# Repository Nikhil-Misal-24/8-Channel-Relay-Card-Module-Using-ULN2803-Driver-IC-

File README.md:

ULN2803 Based 8-Channel Relay Driver Module
8-Channel Relay Card Using ULN2803 Darlington Driver

This project presents the design and implementation of an 8-Channel Relay Driver Module using the ULN2803 Darlington Transistor Array. 
The module is designed to allow low-power microcontroller signals to safely control high-voltage or high-current loads such as lamps, motors, 
fans, and other electrical devices.
The ULN2803 IC acts as a relay driver, enabling reliable switching by amplifying the current from digital control signals. This design 
simplifies interfacing with microcontrollers like Arduino, ESP32, Raspberry Pi, AVR, and PIC, making it ideal for embedded systems and automation applications.
The PCB is designed to provide a compact, efficient, and easy-to-integrate relay control solution for projects involving home automation, industrial control, 
IoT systems, and smart devices.

Key Features
8-Channel relay control system
Driver circuit based on ULN2803 Darlington array
Compatible with microcontrollers (Arduino, ESP32, Raspberry Pi)
Built-in flyback diode protection for relay coils
Compact and reliable PCB layout
Suitable for high-voltage load switching

Applications
Home Automation Systems
Industrial Control Panels
IoT-based Switching Systems
Smart Agriculture Projects
Motor and Pump Control
Lighting Control Systems

Repository Includes
Schematic Design
PCB Layout Files
Gerber Files for PCB Manufacturing
Bill of Materials (BOM)

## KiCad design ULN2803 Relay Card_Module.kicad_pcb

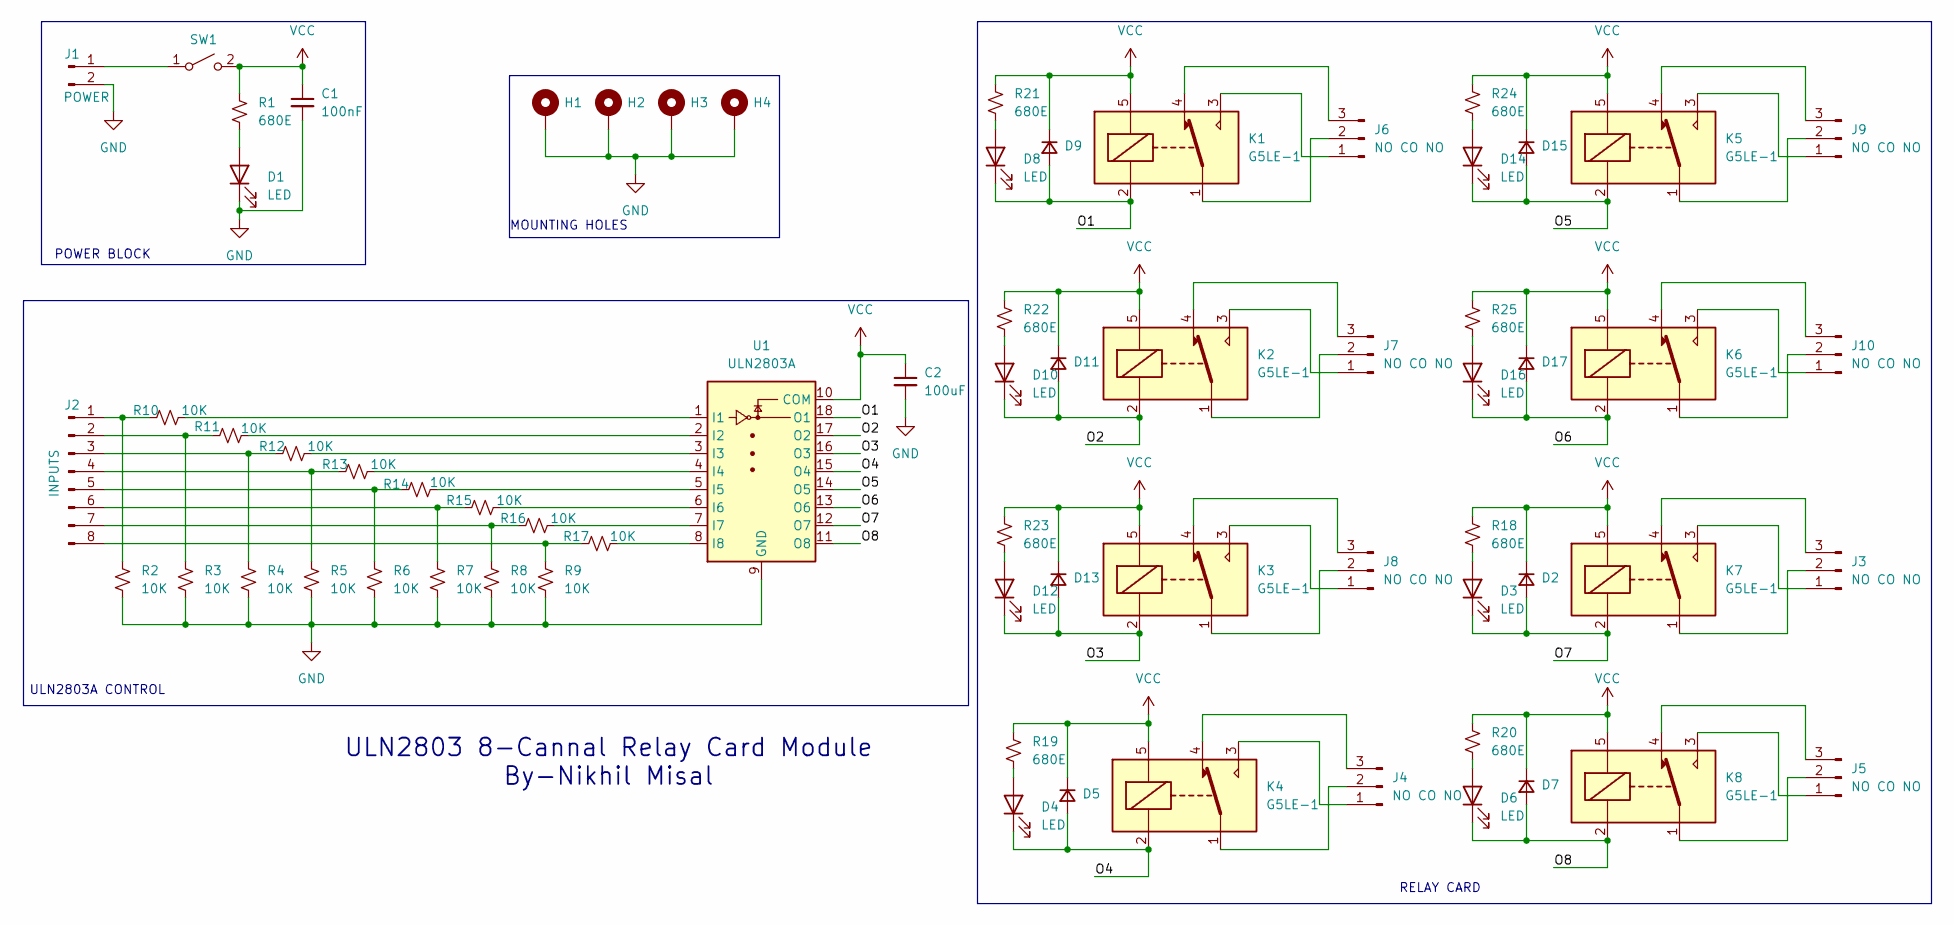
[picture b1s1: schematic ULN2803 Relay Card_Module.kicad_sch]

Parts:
C1: 100nF; C_0805_2012Metric
C2: 100uF; C_0805_2012Metric
D1, D3, D4, D6, D8, D10, D12, D14, D16: LED; LED_1206_3216Metric
D2, D5, D7, D9, D11, D13, D15, D17: D_Small; D_1206_3216Metric
H1, H2, H3, H4: MountingHole_Pad; MountingHole_2.5mm_Pad_Via
J1: POWER; JST_NV_B02P-NV_1x02_P5.00mm_Vertical
J2: INPUTS; PinHeader_1x08_P2.54mm_Vertical
J3, J4, J5, J6, J7, J8, J9, J10: NO CO NO; JST_NV_B03P-NV_1x03_P5.00mm_Vertical
K1, K2, K3, K4, K5, K6, K7, K8: G5LE-1; Relay_SPDT_Omron-G5LE-1
R1, R18, R19, R20, R21, R22, R23, R24, R25: 680E; R_0805_2012Metric
R2, R3, R4, R5, R6, R7, R8, R9, R10, R11, R12, R13, R14, R15, R16, R17: 10K; R_0805_2012Metric
SW1: SW_SPST; SW_DIP_SPSTx01_Slide_6.7x4.1mm_W6.73mm_P2.54mm_LowProfile_J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
U1: ULN2803A; DIP-18_W7.62mm_LongPads

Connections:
/O1: D8.1 (K), D9.2 (A), K1.2, U1.18 (O1)
/O2: D10.1 (K), D11.2 (A), K2.2, U1.17 (O2)
/O3: D12.1 (K), D13.2 (A), K3.2, U1.16 (O3)
/O4: D4.1 (K), D5.2 (A), K4.2, U1.15 (O4)
/O5: D14.1 (K), D15.2 (A), K5.2, U1.14 (O5)
/O6: D16.1 (K), D17.2 (A), K6.2, U1.13 (O6)
/O7: D2.2 (A), D3.1 (K), K7.2, U1.12 (O7)
/O8: D6.1 (K), D7.2 (A), K8.2, U1.11 (O8)
GND: C1.2, C2.2, D1.1 (K), H1.1, H2.1, H3.1, H4.1, J1.2, R2.2, R3.2, R4.2, R5.2, R6.2, R7.2, R8.2, R9.2, U1.9 (GND)
unnamed: D1.2 (A), R1.2
unnamed: D3.2 (A), R18.2
unnamed: D4.2 (A), R19.2
unnamed: D6.2 (A), R20.2
unnamed: D8.2 (A), R21.2
unnamed: D10.2 (A), R22.2
unnamed: D12.2 (A), R23.2
unnamed: D14.2 (A), R24.2
unnamed: D16.2 (A), R25.2
unnamed: J1.1, SW1.1 (A)
unnamed: J2.1, R2.1, R10.1
unnamed: J2.2, R3.1, R11.1
unnamed: J2.3, R4.1, R12.1
unnamed: J2.4, R5.1, R13.1
unnamed: J2.5, R6.1, R14.1
unnamed: J2.6, R7.1, R15.1
unnamed: J2.7, R8.1, R16.1
unnamed: J2.8, R9.1, R17.1
unnamed: J3.1, K7.3
unnamed: J3.2, K7.1
unnamed: J3.3, K7.4
unnamed: J4.1, K4.3
unnamed: J4.2, K4.1
unnamed: J4.3, K4.4
unnamed: J5.1, K8.3
unnamed: J5.2, K8.1
unnamed: J5.3, K8.4
unnamed: J6.1, K1.3
unnamed: J6.2, K1.1
unnamed: J6.3, K1.4
unnamed: J7.1, K2.3
unnamed: J7.2, K2.1
unnamed: J7.3, K2.4
unnamed: J8.1, K3.3
unnamed: J8.2, K3.1
unnamed: J8.3, K3.4
unnamed: J9.1, K5.3
unnamed: J9.2, K5.1
unnamed: J9.3, K5.4
unnamed: J10.1, K6.3
unnamed: J10.2, K6.1
unnamed: J10.3, K6.4
unnamed: R10.2, U1.1 (I1)
unnamed: R11.2, U1.2 (I2)
unnamed: R12.2, U1.3 (I3)
unnamed: R13.2, U1.4 (I4)
unnamed: R14.2, U1.5 (I5)
unnamed: R15.2, U1.6 (I6)
unnamed: R16.2, U1.7 (I7)
unnamed: R17.2, U1.8 (I8)
VCC: C1.1, C2.1, D2.1 (K), D5.1 (K), D7.1 (K), D9.1 (K), D11.1 (K), D13.1 (K), D15.1 (K), D17.1 (K), K1.5, K2.5, K3.5, K4.5, K5.5, K6.5, K7.5, K8.5, R1.1, R18.1, R19.1, R20.1, R21.1, R22.1, R23.1, R24.1, R25.1, SW1.2 (B), U1.10 (COM)

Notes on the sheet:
RELAY CARD
ULN2803A CONTROL
POWER BLOCK
MOUNTING HOLES
ULN2803 8-Cannal Relay Card Module By-Nikhil Misal

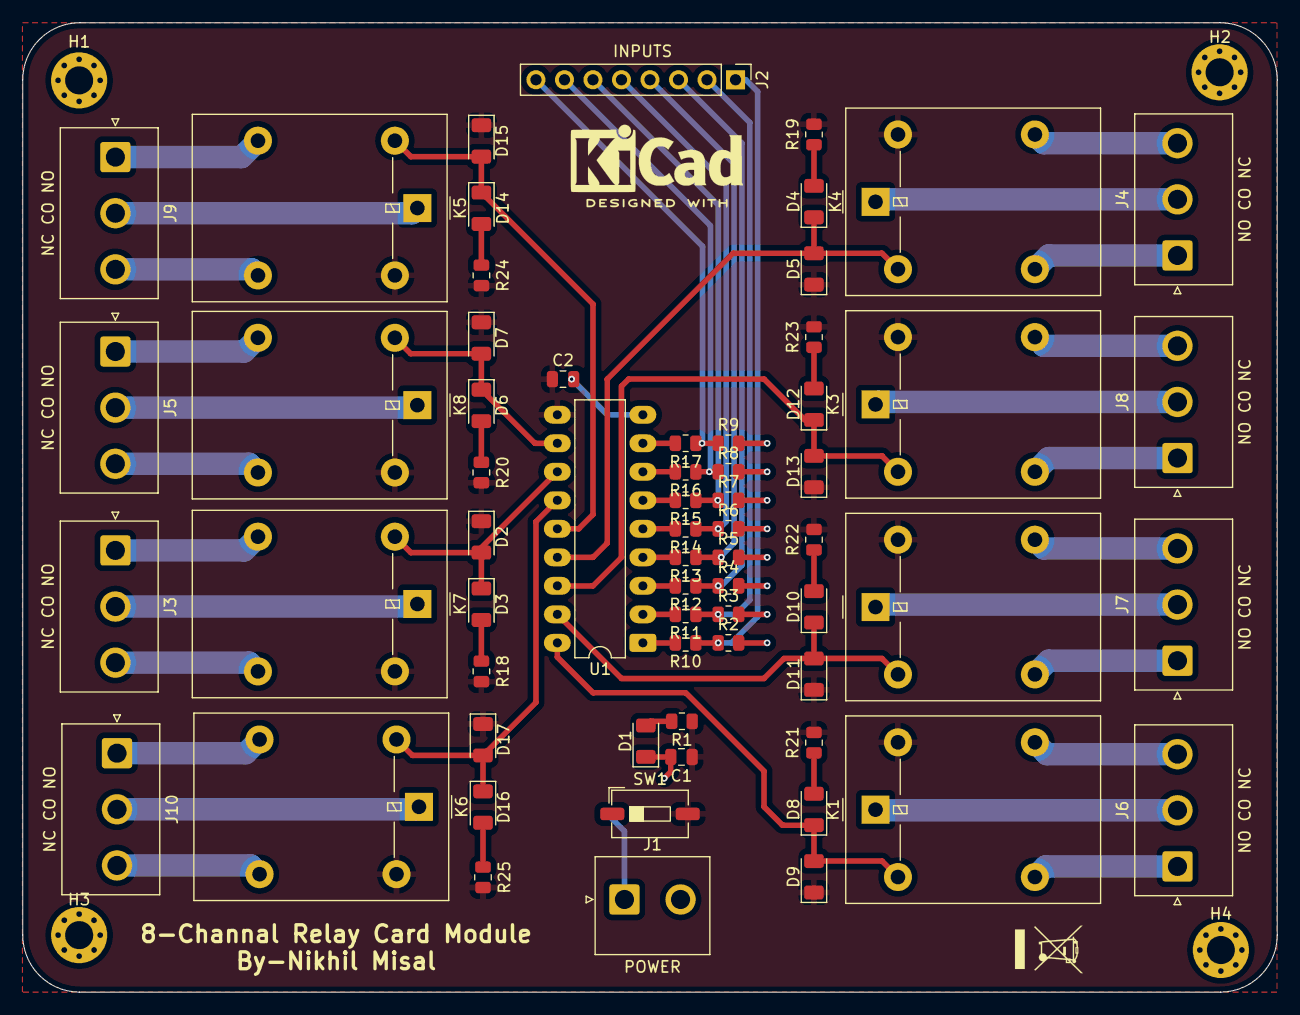
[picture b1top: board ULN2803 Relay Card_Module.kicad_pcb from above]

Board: 2 copper layers, 111.8 x 86.4 mm, 68 parts (0 on the bottom side), 60 nets.

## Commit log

2026-03-05 nikhil commit
2026-03-05 Add project overview and details to README
    Added detailed project description, key features, applications, and repository contents for the ULN2803 Based 8-Channel Relay Driver Module.
